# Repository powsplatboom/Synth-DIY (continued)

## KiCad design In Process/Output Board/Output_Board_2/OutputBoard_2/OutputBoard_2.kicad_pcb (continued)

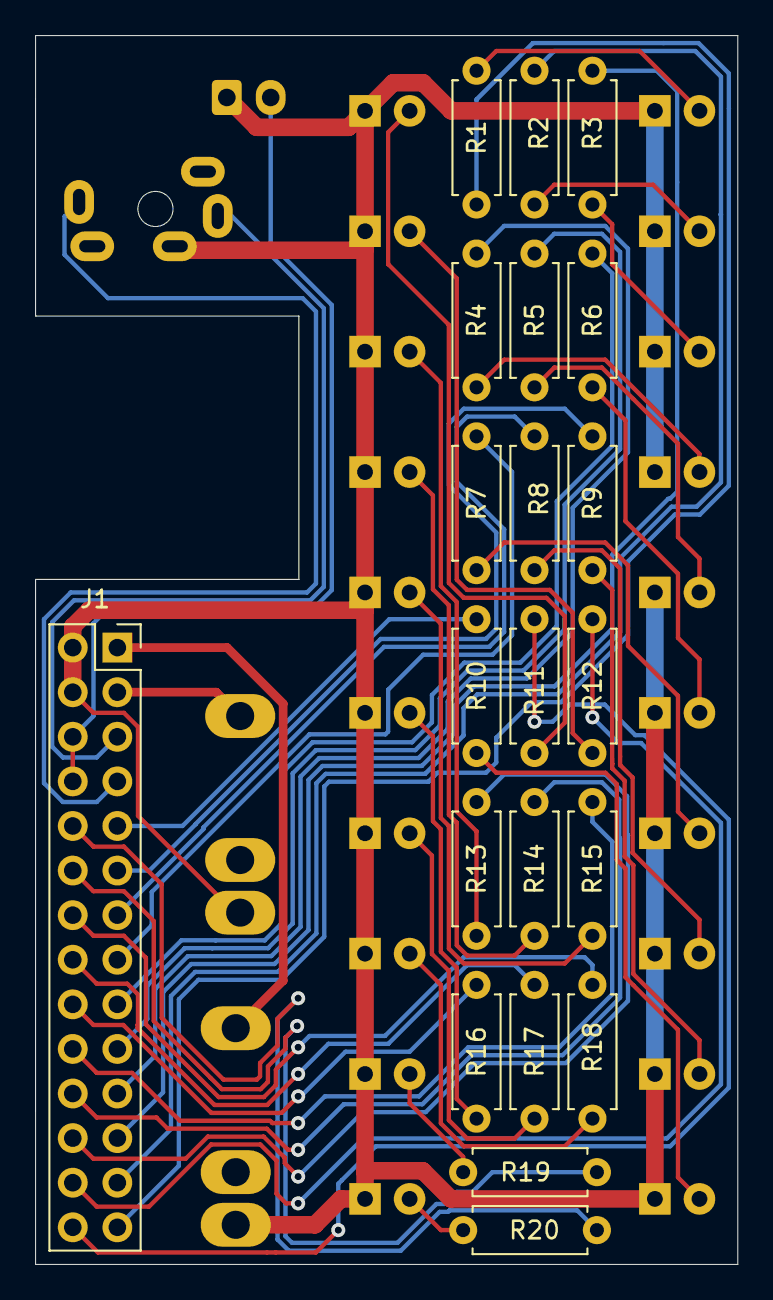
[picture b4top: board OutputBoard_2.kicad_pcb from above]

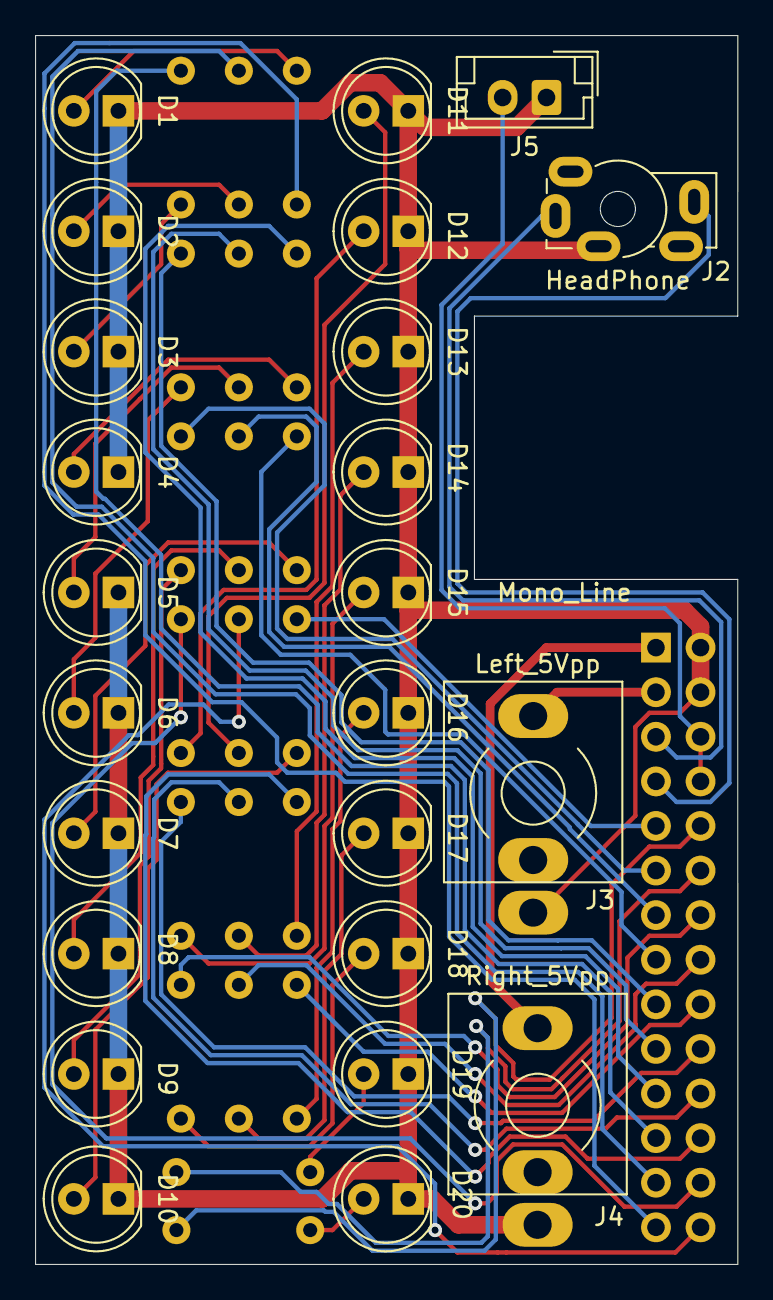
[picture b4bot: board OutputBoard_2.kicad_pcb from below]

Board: 2 copper layers, 40.0 x 70.0 mm, 45 parts (24 on the bottom side), 46 nets.

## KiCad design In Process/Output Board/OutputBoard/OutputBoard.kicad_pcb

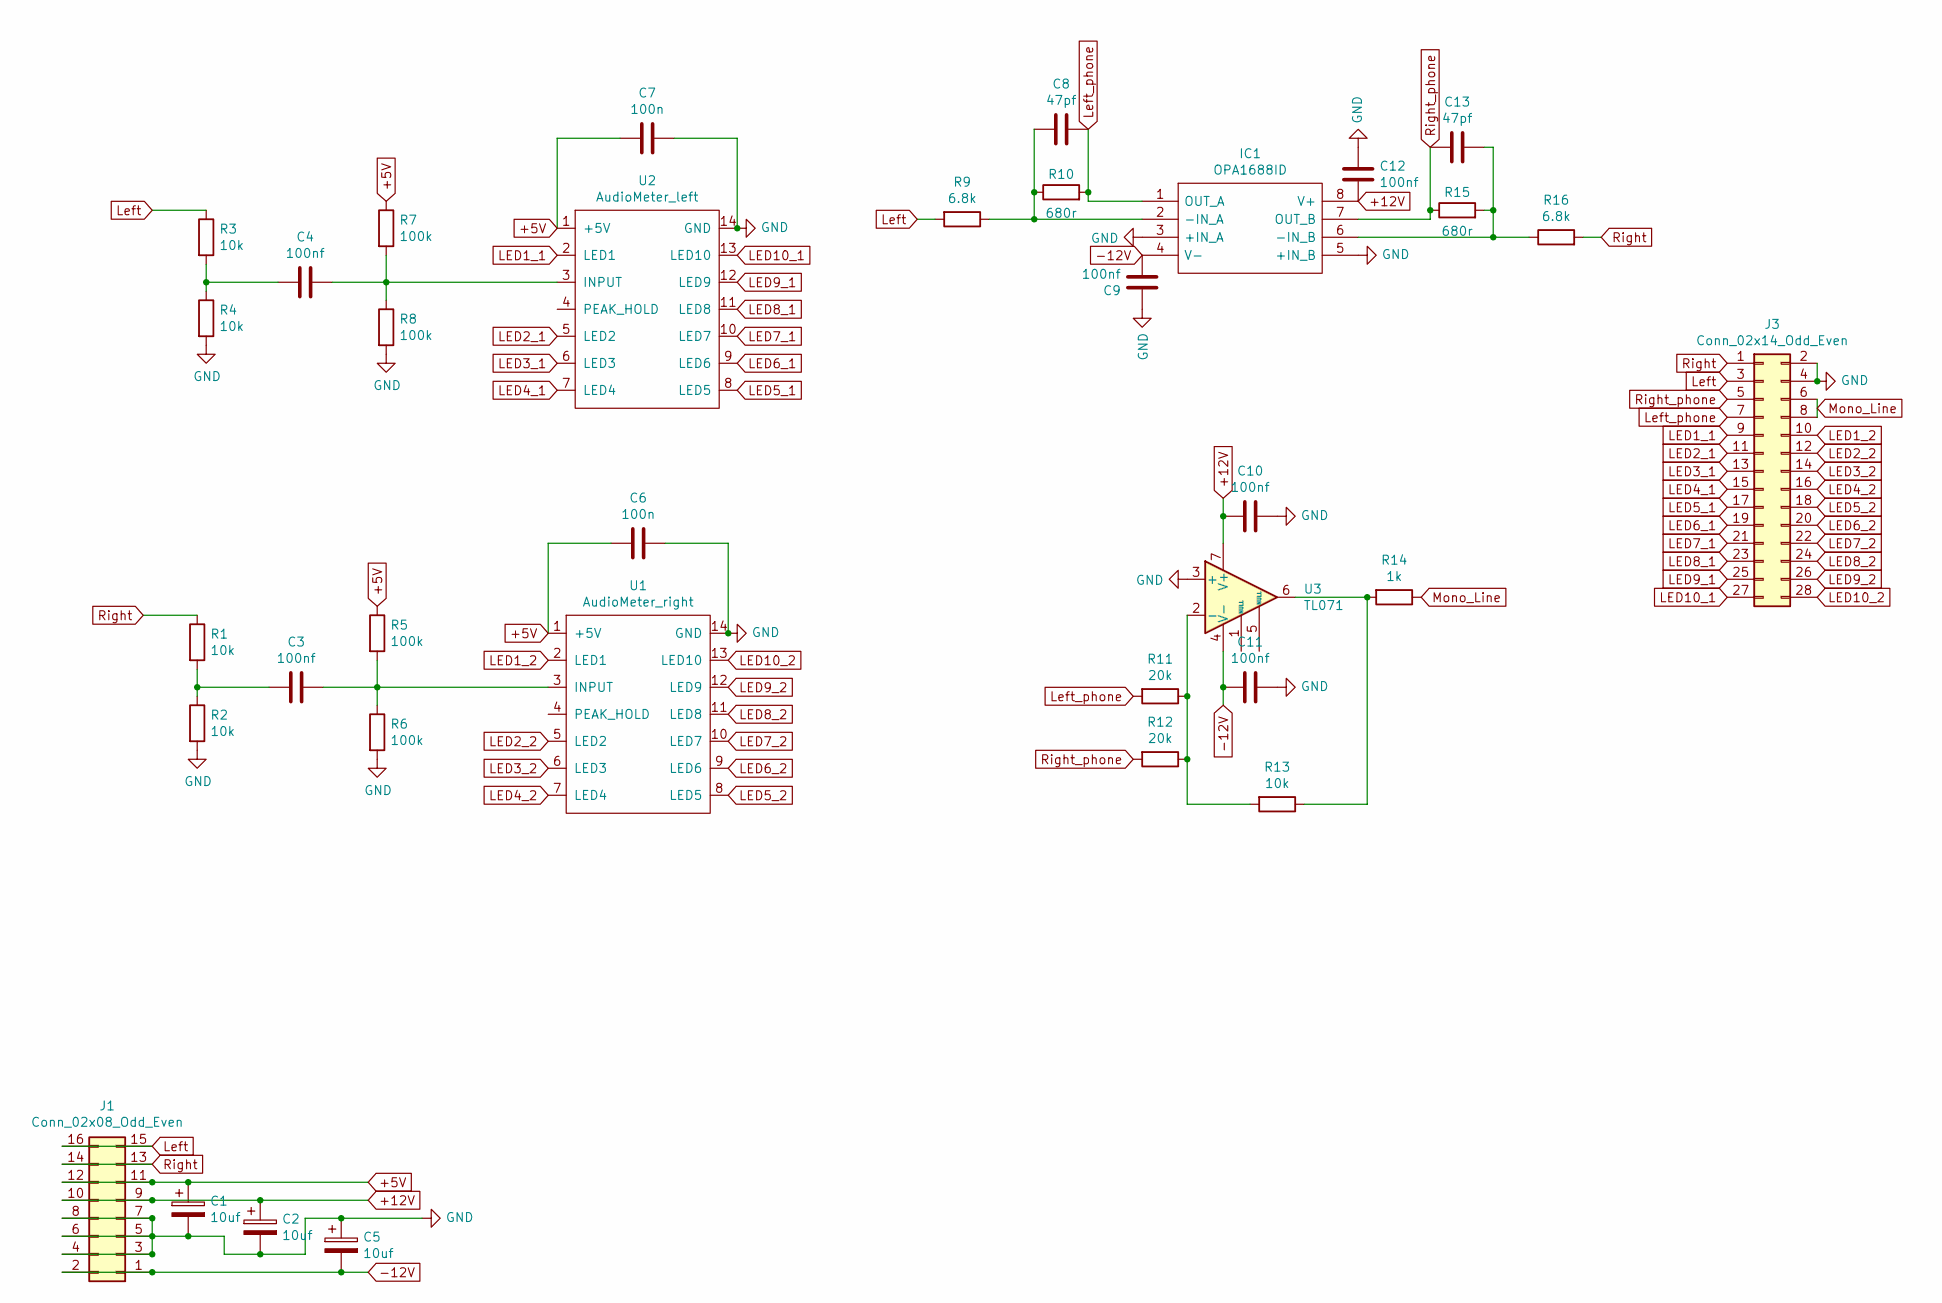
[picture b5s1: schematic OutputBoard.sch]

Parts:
C1, C2, C5: 10uf; CP_Radial_D5.0mm_P2.50mm
C3, C4, C9, C10, C11, C12: 100nf; C_Disc_D4.7mm_W2.5mm_P5.00mm
C6, C7: 100n; C_Disc_D4.7mm_W2.5mm_P5.00mm
C8, C13: 47pf; C_Disc_D4.7mm_W2.5mm_P5.00mm
IC1: OPA1688ID; SOIC-8_3.9x4.9mm_P1.27mm; Manufacturer_Part_Number OPA1688ID; Mouser Part Number 595-OPA1688ID
J1: Conn_02x08_Odd_Even; IDC-Header_2x08_P2.54mm_Vertical
J3: Conn_02x14_Odd_Even; PinHeader_2x14_P2.54mm_Vertical
R1, R2, R3, R4, R13: 10k; R_Axial_DIN0204_L3.6mm_D1.6mm_P7.62mm_Horizontal
R5, R6, R7, R8: 100k; R_Axial_DIN0204_L3.6mm_D1.6mm_P7.62mm_Horizontal
R9, R16: 6.8k; R_Axial_DIN0204_L3.6mm_D1.6mm_P7.62mm_Horizontal
R10, R15: 680r; R_Axial_DIN0204_L3.6mm_D1.6mm_P7.62mm_Horizontal
R11, R12: 20k; R_Axial_DIN0204_L3.6mm_D1.6mm_P7.62mm_Horizontal
R14: 1k; R_Axial_DIN0204_L3.6mm_D1.6mm_P7.62mm_Horizontal
U1: AudioMeter_right; DIP-14_W7.62mm_Socket_LongPads
U2: AudioMeter_left; DIP-14_W7.62mm_Socket_LongPads
U3: TL071; DIP-8_W7.62mm_Socket_LongPads

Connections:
+5V: C1.1, C6.1, C7.1, J1.11, J1.12, R5.1, R7.1, U1.1 (+5V), U2.1 (+5V)
+12V: C2.1, C10.2, C12.2, IC1.8 (V+), J1.9, J1.10, U3.7 (V+)
-12V: C5.2, C9.2, C11.2, IC1.4 (V-), J1.1, J1.2, U3.4 (V-)
GND: C1.2, C2.2, C5.1, C6.2, C7.2, C9.1, C10.1, C11.1, C12.1, IC1.3 (+IN_A), IC1.5 (+IN_B), J1.3, J1.4, J1.5, J1.6, J1.7, J1.8, J3.2, J3.4, R2.2, R4.2, R6.2, R8.2, U1.14 (GND), U2.14 (GND), U3.3 (+)
LED1_1: J3.9, U2.2 (LED1)
LED1_2: J3.10, U1.2 (LED1)
LED2_1: J3.11, U2.5 (LED2)
LED2_2: J3.12, U1.5 (LED2)
LED3_1: J3.13, U2.6 (LED3)
LED3_2: J3.14, U1.6 (LED3)
LED4_1: J3.15, U2.7 (LED4)
LED4_2: J3.16, U1.7 (LED4)
LED5_1: J3.17, U2.8 (LED5)
LED5_2: J3.18, U1.8 (LED5)
LED6_1: J3.19, U2.9 (LED6)
LED6_2: J3.20, U1.9 (LED6)
LED7_1: J3.21, U2.10 (LED7)
LED7_2: J3.22, U1.10 (LED7)
LED8_1: J3.23, U2.11 (LED8)
LED8_2: J3.24, U1.11 (LED8)
LED9_1: J3.25, U2.12 (LED9)
LED9_2: J3.26, U1.12 (LED9)
LED10_1: J3.27, U2.13 (LED10)
LED10_2: J3.28, U1.13 (LED10)
Left: J1.15, J1.16, J3.3, R3.1, R9.2
Left_phone: C8.1, IC1.1 (OUT_A), J3.7, R10.2, R11.2
Mono_Line: J3.6, J3.8, R14.1
unnamed: C3.1, R5.2, R6.1, U1.3 (INPUT)
unnamed: C3.2, R1.2, R2.1
unnamed: C4.1, R7.2, R8.1, U2.3 (INPUT)
unnamed: C4.2, R3.2, R4.1
unnamed: C8.2, IC1.2 (-IN_A), R9.1, R10.1
unnamed: C13.1, IC1.6 (-IN_B), R15.2, R16.1
unnamed: R11.1, R12.1, R13.2, U3.2 (-)
unnamed: R13.1, R14.2, U3.6
Right: J1.13, J1.14, J3.1, R1.1, R16.2
Right_phone: C13.2, IC1.7 (OUT_B), J3.5, R12.2, R15.1

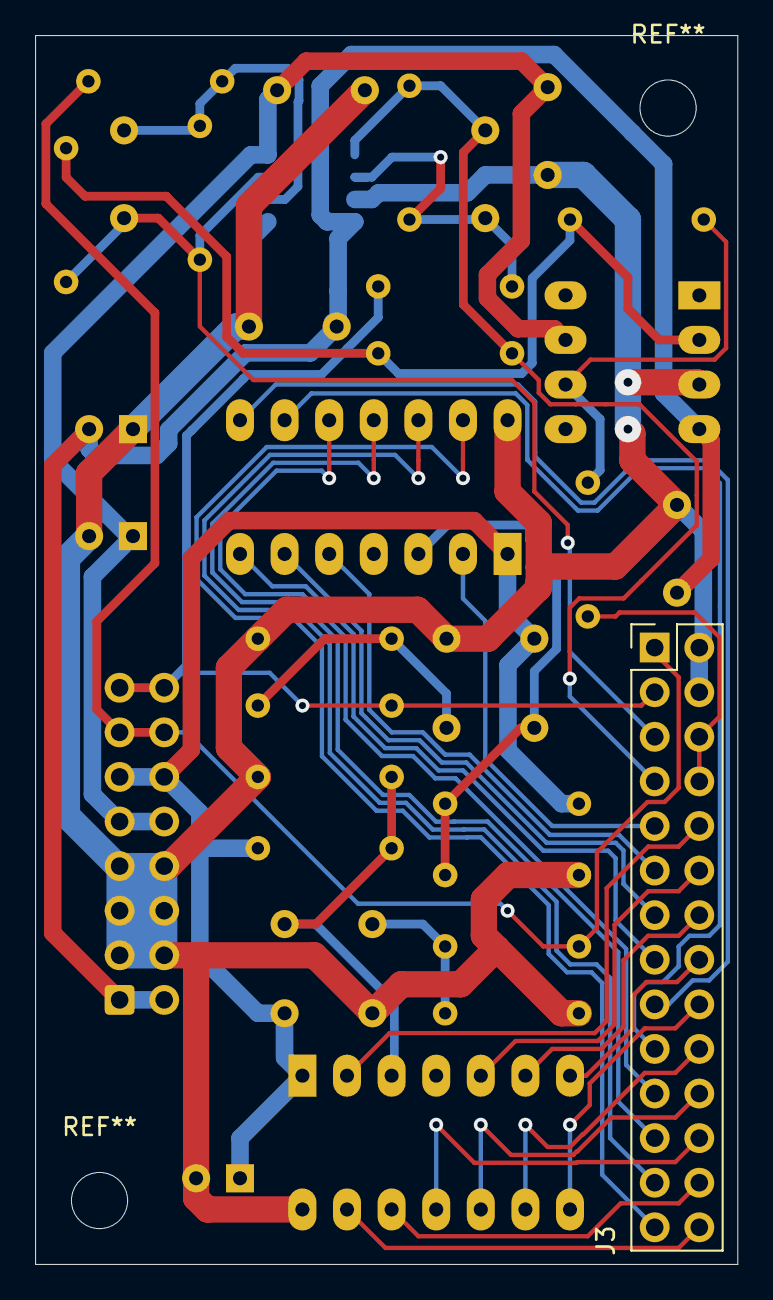
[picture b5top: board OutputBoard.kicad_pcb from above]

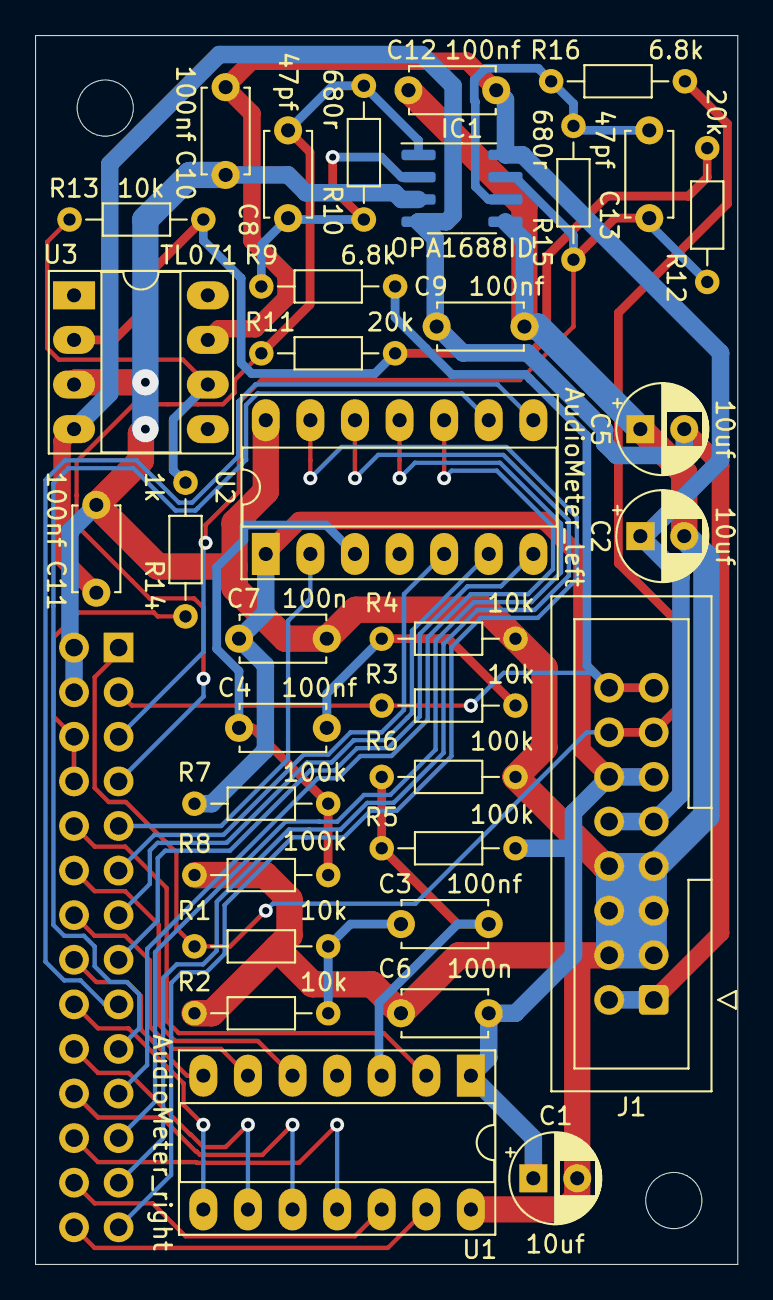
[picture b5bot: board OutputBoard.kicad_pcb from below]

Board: 2 copper layers, 40.0 x 70.0 mm, 35 parts (34 on the bottom side), 37 nets.
